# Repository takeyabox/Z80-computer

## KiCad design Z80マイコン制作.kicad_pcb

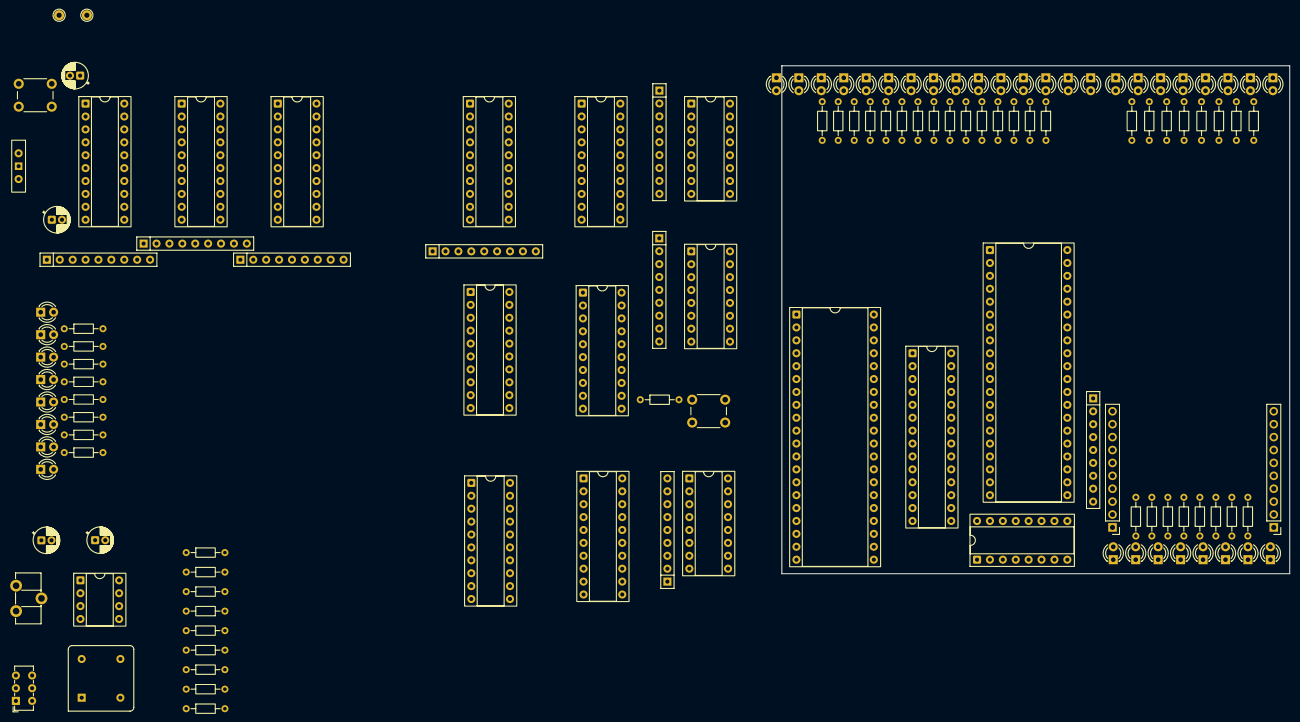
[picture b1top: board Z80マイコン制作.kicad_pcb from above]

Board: 2 copper layers, 100.0 x 100.0 mm, 127 parts (0 on the bottom side), 165 nets, no tracks yet.

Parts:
0.01uF, 0.01uF#2: 0.01u; CP_Radial_D5.0mm_P2.00mm
10uF: 10uF; CP_Radial_D5.0mm_P2.00mm
74HCT244-0, 74HCT244-1, 74HCT244-2, 74HCT244-3, 74HCT244-4, 74HCT244-5, 74HCT244-6, 74HCT244-7, 74HCT244-8: 74HCT244; DIP-20_W7.62mm_Socket
100uF: 100u; CP_Radial_D5.0mm_P2.00mm
A0, A1, A2, A3, A4, A5, A6, A7, A8, A9, A10, A11, A12, A13, A14: LED; LED_D3.0mm
A7-A0, A14-A8: SW_DIP_x08; DIP-16_W7.62mm_Socket
BUSACK: LED; LED_D3.0mm
BUSRQ: SW_DIP_x01; SW_Slide-03_Wuerth-WS-SLTV_10x2.5x6.4_P2.54mm
CLK: LED; LED_D3.0mm
CLOCK ch: SW_Slide_DPDT; SW_E-Switch_EG1271_SPDT
CY7C199: CY7C199; DIP-28_W7.62mm_Socket
D0, D1, D2, D3, D4, D5, D6, D7: LED; LED_D3.0mm
D7-D0: SW_DIP_x08; DIP-16_W7.62mm_Socket
FREQENCY: R_Potentiometer; Potentiometer_ACP_CA9-H5_Horizontal
GND: GND; TestPoint_THTPad_D2.0mm_Drill1.0mm
I7-I0: SW_DIP_x08; DIP-16_W7.62mm_Socket
IORQ: LED; LED_D3.0mm
M1: LED; LED_D3.0mm
MREQ: LED; LED_D3.0mm
O0, O1, O2, O3, O4, O5, O6, O7: LED; LED_D3.0mm
OSCILLATOR: CXO_DIP8; Oscillator_DIP-8
PA: Conn_01x10_Pin; PinHeader_1x10_P2.54mm_Vertical
PB: Conn_01x10_Pin; PinHeader_1x10_P2.54mm_Vertical
R0, R1, R2, R3, R4, R5, R6, R7, R8, R9, R10, R11, R12, R13, R14, R15, R16, R17, R18, R19, R20, R21, R22, R23, R24, R25, R26, R27, R28, R29, R30, R31, R32, R33, R34, R36, R37, R38, R40, R41, R42, R43, R44, R45, R46, R47, R48: 4.7k; R_Axial_DIN0204_L3.6mm_D1.6mm_P7.62mm_Horizontal
R35: 330; R_Axial_DIN0204_L3.6mm_D1.6mm_P7.62mm_Horizontal
R39: 10k; R_Axial_DIN0204_L3.6mm_D1.6mm_P7.62mm_Horizontal
RD: LED; LED_D3.0mm
RESET: SW_Push; SW_PUSH_6mm
RN0, RN1, RN2, RN3, RN4, RN5, RN7, RN8: 4.7k; R_Array_SIP9
UNE555P: NE555P; DIP-8_W7.62mm_Socket
VCC: VCC; TestPoint_THTPad_D2.0mm_Drill1.0mm
WAIT: LED; LED_D3.0mm
WR: LED; LED_D3.0mm
WRITE: SW_Push; SW_PUSH_6mm
Z80 CPU: Z80CPU; DIP-40_W15.24mm_Socket
Z80PIO: Z8420; DIP-40_W15.24mm_Socket

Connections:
GND: 10uF.2, 74HCT244-0.10 (GND), 74HCT244-1.10 (GND), 74HCT244-2.10 (GND), 74HCT244-3.10 (GND), 74HCT244-4.10 (GND), 74HCT244-5.6 (1A2), 74HCT244-5.10 (GND), 74HCT244-6.10 (GND), 74HCT244-7.10 (GND), 74HCT244-8.10 (GND), 100uF.2, A0.1 (K), A1.1 (K), A2.1 (K), A3.1 (K), A4.1 (K), A5.1 (K), A6.1 (K), A7.1 (K), A7-A0.9, A7-A0.10, A7-A0.11, A7-A0.12, A7-A0.13, A7-A0.14, A7-A0.15, A7-A0.16, A8.1 (K), A9.1 (K), A10.1 (K), A11.1 (K), A12.1 (K), A13.1 (K), A14.1 (K), A14-A8.9, A14-A8.10, A14-A8.11, A14-A8.12, A14-A8.13, A14-A8.14, A14-A8.15, A14-A8.16, BUSACK.1 (K), BUSRQ.1, CLK.1 (K), CLOCK ch.5 (B), CY7C199.14 (GND), D0.1 (K), D1.1 (K), D2.1 (K), D3.1 (K), D4.1 (K), D5.1 (K), D6.1 (K), D7.1 (K), D7-D0.9, D7-D0.10, D7-D0.11, D7-D0.12, D7-D0.13, D7-D0.14, D7-D0.15, D7-D0.16, GND.1, I7-I0.9, I7-I0.10, I7-I0.11, I7-I0.12, I7-I0.13, I7-I0.14, I7-I0.15, I7-I0.16, IORQ.1 (K), M1.1 (K), MREQ.1 (K), O0.1 (K), O1.1 (K), O2.1 (K), O3.1 (K), O4.1 (K), O5.1 (K), O6.1 (K), O7.1 (K), PA.2, PB.2, RD.1 (K), RESET.1, WAIT.1 (K), WR.1 (K), WRITE.2, Z80 CPU.29 (GND), Z80PIO.11 (GND)
unnamed: 74HCT244-7.2 (1A0), Z80PIO.27 (PB0)
unnamed: 74HCT244-7.4 (1A1), Z80PIO.28 (PB1)
unnamed: 74HCT244-7.6 (1A2), Z80PIO.29 (PB2)
unnamed: 74HCT244-7.8 (1A3), Z80PIO.30 (PB3)
unnamed: 74HCT244-7.1 (1OE), 74HCT244-7.19 (2OE), R40.2
unnamed: 74HCT244-7.18 (1Y0), PB.10, R48.2
unnamed: 74HCT244-7.16 (1Y1), PB.9, R47.2
unnamed: 74HCT244-7.14 (1Y2), PB.8, R46.2
unnamed: 74HCT244-7.12 (1Y3), PB.7, R45.2
unnamed: 74HCT244-7.17 (2A0), Z80PIO.31 (PB4)
unnamed: 74HCT244-7.15 (2A1), Z80PIO.32 (PB5)
unnamed: 74HCT244-7.13 (2A2), Z80PIO.33 (PB6)
unnamed: 74HCT244-7.11 (2A3), Z80PIO.34 (PB7)
unnamed: 74HCT244-7.3 (2Y0), PB.6, R44.2
unnamed: 74HCT244-7.5 (2Y1), PB.5, R43.2
unnamed: 74HCT244-7.7 (2Y2), PB.4, R42.2
unnamed: 74HCT244-7.9 (2Y3), PB.3, R41.2
unnamed: A0.2 (A), R0.1
unnamed: A1.2 (A), R1.1
unnamed: A2.2 (A), R2.1
unnamed: A3.2 (A), R3.1
unnamed: A4.2 (A), R4.1
unnamed: A5.2 (A), R5.1
unnamed: A6.2 (A), R6.1
unnamed: A7.2 (A), R7.1
unnamed: A8.2 (A), R8.1
unnamed: A9.2 (A), R9.1
unnamed: A10.2 (A), R10.1
unnamed: A11.2 (A), R11.1
unnamed: A12.2 (A), R12.1
unnamed: A13.2 (A), R13.1
unnamed: A14.2 (A), R14.1
unnamed: BUSACK.2 (A), R30.1
unnamed: CLK.2 (A), R23.1
unnamed: D0.2 (A), R15.1
unnamed: D1.2 (A), R16.1
unnamed: D2.2 (A), R17.1
unnamed: D3.2 (A), R18.1
unnamed: D4.2 (A), R19.1
unnamed: D5.2 (A), R20.1
unnamed: D6.2 (A), R21.1
unnamed: D7.2 (A), R22.1
unnamed: IORQ.2 (A), R29.1
unnamed: I7-I0.8, PA.3, RN7.9 (R8), Z80PIO.7 (PA7)
unnamed: I7-I0.7, PA.4, RN7.8 (R7), Z80PIO.8 (PA6)
unnamed: I7-I0.6, PA.5, RN7.7 (R6), Z80PIO.9 (PA5)
unnamed: I7-I0.5, PA.6, RN7.6 (R5), Z80PIO.10 (PA4)
unnamed: I7-I0.4, PA.7, RN7.5 (R4), Z80PIO.12 (PA3)
unnamed: I7-I0.3, PA.8, RN7.4 (R3), Z80PIO.13 (PA2)
unnamed: I7-I0.2, PA.9, RN7.3 (R2), Z80PIO.14 (PA1)
unnamed: I7-I0.1, PA.10, RN7.2 (R1), Z80PIO.15 (PA0)
unnamed: M1.2 (A), R24.1
unnamed: MREQ.2 (A), R28.1
unnamed: O0.2 (A), R48.1
unnamed: O1.2 (A), R47.1
unnamed: O2.2 (A), R46.1
unnamed: O3.2 (A), R45.1
unnamed: O4.2 (A), R44.1
unnamed: O5.2 (A), R43.1
unnamed: O6.2 (A), R42.1
unnamed: O7.2 (A), R41.1
unnamed: R26.1, RD.2 (A)
unnamed: 74HCT244-0.2 (1A0), CLOCK ch.2 (B), RN0.2 (R1), Z80 CPU.6 (~CLK), Z80PIO.25 (CLK)
unnamed: 74HCT244-0.4 (1A1), RN0.3 (R2), Z80 CPU.27 (~M1), Z80PIO.37 (~M1)
unnamed: 74HCT244-0.6 (1A2), R34.2, RN0.4 (R3), Z80 CPU.17 (~NMI), Z80 CPU.24 (~WAIT)
unnamed: 74HCT244-0.8 (1A3), 74HCT244-5.18 (1Y0), CY7C199.22 (~OE), RN0.5 (R4), Z80 CPU.21 (~RD), Z80PIO.35 (~RD)
unnamed: 74HCT244-0.17 (2A0), 74HCT244-5.16 (1Y1), CY7C199.27 (~WE), RN0.6 (R5), Z80 CPU.22 (~WR)
unnamed: 74HCT244-0.15 (2A1), 74HCT244-5.14 (1Y2), CY7C199.20 (~CE), RN0.7 (R6), Z80 CPU.19 (~MREQ)
unnamed: 74HCT244-0.13 (2A2), RN0.8 (R7), Z80 CPU.20 (~IORQ), Z80PIO.4 (~CE), Z80PIO.36 (~IORQ)
unnamed: 74HCT244-0.11 (2A3), 74HCT244-4.1 (1OE), 74HCT244-4.19 (2OE), 74HCT244-5.1 (1OE), 74HCT244-5.19 (2OE), 74HCT244-6.1 (1OE), 74HCT244-6.19 (2OE), 74HCT244-8.1 (1OE), 74HCT244-8.19 (2OE), RN0.9 (R8), Z80 CPU.23 (~BUSACK)
unnamed: 74HCT244-3.2 (1A0), 74HCT244-8.18 (1Y0), CY7C199.11 (D0), RN1.2 (R1), Z80 CPU.14 (D0), Z80PIO.19 (D0)
unnamed: 74HCT244-3.4 (1A1), 74HCT244-8.16 (1Y1), CY7C199.12 (D1), RN1.3 (R2), Z80 CPU.15 (D1), Z80PIO.20 (D1)
unnamed: 74HCT244-3.6 (1A2), 74HCT244-8.14 (1Y2), CY7C199.13 (D2), RN1.4 (R3), Z80 CPU.12 (D2), Z80PIO.1 (D2)
unnamed: 74HCT244-3.8 (1A3), 74HCT244-8.12 (1Y3), CY7C199.15 (D3), RN1.5 (R4), Z80 CPU.8 (D3), Z80PIO.40 (D3)
unnamed: 74HCT244-3.17 (2A0), 74HCT244-8.3 (2Y0), CY7C199.16 (D4), RN1.6 (R5), Z80 CPU.7 (D4), Z80PIO.39 (D4)
unnamed: 74HCT244-3.15 (2A1), 74HCT244-8.5 (2Y1), CY7C199.17 (D5), RN1.7 (R6), Z80 CPU.9 (D5), Z80PIO.38 (D5)
unnamed: 74HCT244-3.13 (2A2), 74HCT244-8.7 (2Y2), CY7C199.18 (D6), RN1.8 (R7), Z80 CPU.10 (D6), Z80PIO.3 (D6)
unnamed: 74HCT244-3.11 (2A3), 74HCT244-8.9 (2Y3), CY7C199.19 (D7), RN1.9 (R8), Z80 CPU.13 (D7), Z80PIO.2 (D7)
unnamed: 74HCT244-1.2 (1A0), 74HCT244-6.18 (1Y0), CY7C199.4 (A8), RN2.2 (R1), Z80 CPU.38 (A8)
unnamed: 74HCT244-1.4 (1A1), 74HCT244-6.16 (1Y1), CY7C199.5 (A9), RN2.3 (R2), Z80 CPU.39 (A9)
unnamed: 74HCT244-1.6 (1A2), 74HCT244-6.14 (1Y2), CY7C199.6 (A10), RN2.4 (R3), Z80 CPU.40 (A10)
unnamed: 74HCT244-1.8 (1A3), 74HCT244-6.12 (1Y3), CY7C199.7 (A11), RN2.5 (R4), Z80 CPU.1 (A11)
unnamed: 74HCT244-1.17 (2A0), 74HCT244-6.3 (2Y0), CY7C199.8 (A12), RN2.6 (R5), Z80 CPU.2 (A12)
unnamed: 74HCT244-1.15 (2A1), 74HCT244-6.5 (2Y1), CY7C199.9 (A13), RN2.7 (R6), Z80 CPU.3 (A13)
unnamed: 74HCT244-1.13 (2A2), 74HCT244-6.7 (2Y2), CY7C199.10 (A14), RN2.8 (R7), Z80 CPU.4 (A14)
unnamed: 74HCT244-2.2 (1A0), 74HCT244-4.18 (1Y0), CY7C199.21 (A0), RN3.2 (R1), Z80 CPU.30 (A0), Z80PIO.6 (B/~A)
unnamed: 74HCT244-2.4 (1A1), 74HCT244-4.16 (1Y1), CY7C199.23 (A1), RN3.3 (R2), Z80 CPU.31 (A1), Z80PIO.5 (C/~D)
unnamed: 74HCT244-2.6 (1A2), 74HCT244-4.14 (1Y2), CY7C199.24 (A2), RN3.4 (R3), Z80 CPU.32 (A2)
unnamed: 74HCT244-2.8 (1A3), 74HCT244-4.12 (1Y3), CY7C199.25 (A3), RN3.5 (R4), Z80 CPU.33 (A3)
unnamed: 74HCT244-2.17 (2A0), 74HCT244-4.3 (2Y0), CY7C199.26 (A4), RN3.6 (R5), Z80 CPU.34 (A4)
unnamed: 74HCT244-2.15 (2A1), 74HCT244-4.5 (2Y1), CY7C199.1 (A5), RN3.7 (R6), Z80 CPU.35 (A5)
unnamed: 74HCT244-2.13 (2A2), 74HCT244-4.7 (2Y2), CY7C199.2 (A6), RN3.8 (R7), Z80 CPU.36 (A6)
unnamed: 74HCT244-2.11 (2A3), 74HCT244-4.9 (2Y3), CY7C199.3 (A7), RN3.9 (R8), Z80 CPU.37 (A7)
unnamed: 74HCT244-6.2 (1A0), A14-A8.1, RN4.2 (R1)
unnamed: 74HCT244-6.4 (1A1), A14-A8.2, RN4.3 (R2)
unnamed: 74HCT244-6.6 (1A2), A14-A8.3, RN4.4 (R3)
unnamed: 74HCT244-6.8 (1A3), A14-A8.4, RN4.5 (R4)
unnamed: 74HCT244-6.17 (2A0), A14-A8.5, RN4.6 (R5)
unnamed: 74HCT244-6.15 (2A1), A14-A8.6, RN4.7 (R6)
unnamed: 74HCT244-6.13 (2A2), A14-A8.7, RN4.8 (R7)
unnamed: 74HCT244-4.2 (1A0), A7-A0.1, RN5.2 (R1)
unnamed: 74HCT244-4.4 (1A1), A7-A0.2, RN5.3 (R2)
unnamed: 74HCT244-4.6 (1A2), A7-A0.3, RN5.4 (R3)
unnamed: 74HCT244-4.8 (1A3), A7-A0.4, RN5.5 (R4)
unnamed: 74HCT244-4.17 (2A0), A7-A0.5, RN5.6 (R5)
unnamed: 74HCT244-4.15 (2A1), A7-A0.6, RN5.7 (R6)
unnamed: 74HCT244-4.13 (2A2), A7-A0.7, RN5.8 (R7)
unnamed: 74HCT244-4.11 (2A3), A7-A0.8, RN5.9 (R8)
unnamed: 74HCT244-8.11 (2A3), D7-D0.8, RN8.2 (R1)
unnamed: 74HCT244-8.13 (2A2), D7-D0.7, RN8.3 (R2)
unnamed: 74HCT244-8.15 (2A1), D7-D0.6, RN8.4 (R3)
unnamed: 74HCT244-8.17 (2A0), D7-D0.5, RN8.5 (R4)
unnamed: 74HCT244-8.8 (1A3), D7-D0.4, RN8.6 (R5)
unnamed: 74HCT244-8.6 (1A2), D7-D0.3, RN8.7 (R6)
unnamed: 74HCT244-8.4 (1A1), D7-D0.2, RN8.8 (R7)
unnamed: 74HCT244-8.2 (1A0), D7-D0.1, RN8.9 (R8)
unnamed: 74HCT244-0.1 (1OE), 74HCT244-0.19 (2OE), 74HCT244-1.1 (1OE), 74HCT244-1.19 (2OE), 74HCT244-2.1 (1OE), 74HCT244-2.19 (2OE), 74HCT244-3.1 (1OE), 74HCT244-3.19 (2OE), R31.2
unnamed: 74HCT244-2.18 (1Y0), R0.2
unnamed: 74HCT244-2.16 (1Y1), R1.2
unnamed: 74HCT244-2.14 (1Y2), R2.2
unnamed: 74HCT244-2.12 (1Y3), R3.2
unnamed: 74HCT244-2.3 (2Y0), R4.2
unnamed: 74HCT244-2.5 (2Y1), R5.2
unnamed: 74HCT244-2.7 (2Y2), R6.2
unnamed: 74HCT244-2.9 (2Y3), R7.2
unnamed: 74HCT244-1.18 (1Y0), R8.2
unnamed: 74HCT244-1.16 (1Y1), R9.2
unnamed: 74HCT244-1.14 (1Y2), R10.2
unnamed: 74HCT244-1.12 (1Y3), R11.2
unnamed: 74HCT244-1.3 (2Y0), R12.2
unnamed: 74HCT244-1.5 (2Y1), R13.2
unnamed: 74HCT244-1.7 (2Y2), R14.2
unnamed: 74HCT244-3.18 (1Y0), R15.2
unnamed: 74HCT244-3.16 (1Y1), R16.2
unnamed: 74HCT244-3.14 (1Y2), R17.2
unnamed: 74HCT244-3.12 (1Y3), R18.2
unnamed: 74HCT244-3.3 (2Y0), R19.2
unnamed: 74HCT244-3.5 (2Y1), R20.2
unnamed: 74HCT244-3.7 (2Y2), R21.2
unnamed: 74HCT244-3.9 (2Y3), R22.2
unnamed: 74HCT244-0.18 (1Y0), R23.2
unnamed: 74HCT244-0.16 (1Y1), R24.2
unnamed: 74HCT244-0.14 (1Y2), R25.2
unnamed: 74HCT244-0.12 (1Y3), R26.2
unnamed: 74HCT244-0.3 (2Y0), R27.2
unnamed: 74HCT244-0.5 (2Y1), R28.2
unnamed: 74HCT244-0.7 (2Y2), R29.2
unnamed: 74HCT244-0.9 (2Y3), R30.2
unnamed: BUSRQ.2, R33.2, Z80 CPU.25 (~BUSRQ)
unnamed: Z80 CPU.16 (~INT), Z80PIO.23 (~INT)
unnamed: 10uF.1, R32.2, RESET.2, Z80 CPU.26 (~RESET)
unnamed: 74HCT244-5.2 (1A0), R37.2
unnamed: 74HCT244-5.4 (1A1), R38.2, WRITE.1
unnamed: 0.01uF.1, CLOCK ch.4 (A), UNE555P.5 (CV)
unnamed: FREQENCY.3, R39.2, UNE555P.7 (DIS)
unnamed: 0.01uF.2, 0.01uF#2.2, UNE555P.1 (GND)
unnamed: CLOCK ch.3 (C), UNE555P.3 (Q)
unnamed: 0.01uF#2.1, FREQENCY.2, UNE555P.2 (TR), UNE555P.6 (THR)
unnamed: R25.1, WAIT.2 (A)
unnamed: R27.1, WR.2 (A)
unnamed: CLOCK ch.6 (C), OSCILLATOR.4 (GND)
unnamed: CLOCK ch.1 (A), OSCILLATOR.5 (OUT), R35.1
unnamed: R36.2, Z80PIO.24 (IEI)
VCC: 74HCT244-0.20 (VCC), 74HCT244-1.20 (VCC), 74HCT244-2.20 (VCC), 74HCT244-3.20 (VCC), 74HCT244-4.20 (VCC), 74HCT244-5.20 (VCC), 74HCT244-6.20 (VCC), 74HCT244-7.20 (VCC), 74HCT244-8.20 (VCC), 100uF.1, CY7C199.28 (VCC), OSCILLATOR.8 (Vcc), PA.1, PB.1, R31.1, R32.1, R33.1, R34.1, R35.2, R36.1, R37.1, R38.1, R39.1, R40.1, RN0.1 (common), RN1.1 (common), RN2.1 (common), RN3.1 (common), RN4.1 (common), RN5.1 (common), RN7.1 (common), RN8.1 (common), UNE555P.4 (R), UNE555P.8 (VCC), VCC.1, Z80 CPU.11 (VCC), Z80PIO.26 (VCC)

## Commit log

2025-07-31 Add files via upload
    NEW project
2025-07-31 Add files via upload
    parts property
2025-09-06 回路図を作りました。まだ確認してません
2025-09-06 基盤確認済み、PCBに入りました
2025-09-08 ちょっと変えた
2025-09-08 基盤のVCC,GND配線終わりました
2025-09-08 ちょっと変更
2025-09-08 基盤完成
2025-09-10 今度こそ基盤完成！！
2025-09-10 製造用ファイルたち
2025-09-13 最後にしたい
2025-12-12 add gitingore
2025-12-12 start designing
